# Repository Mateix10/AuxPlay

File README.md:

# AuxPlay
A esp32 based AirPlay receiver for powered speakers. 

Note: This DOES NOT include a amplifier, please connect this device to powered speakers or a speaker amplifier.

# Why?

I always wanted to play music wirelessly to my stereo. It was made in 2001 and it obviously does not have Bluetooth or AirPlay, so I decided to make a device that adds that functionality to it.

# Zine

# Schematic and PCB

For the "brains" I used a older esp32 module because the newer ones don't have classic bluetooth, required for Bluetooth A2DP, aka sound.

For the DAC, I used a PCM-5102 breakout board. Chose it for its sound quality. I used the breakout board for the extra filtering found on there and the ease of soldering it onto the PCB.

The PJ-320B 3.5mm headphone jack is connected through the PCB, using the pins on the DAC breakout board.

# Case

For the case I used Fusion 360. The top part of the case along with the motherboard is screwed in with m2 screws. Preferably, the screws should be long (about 14mm) so it can reach the PCB along with the inserts at the bottom.

# Firmware

For the firmware, I am using [airplay-esp32 by rbouteiller](https://github.com/rbouteiller/airplay-esp32).

# BOM

|Product|Count|Cost|Link|
|--|--|--|--|
|Esp32|1|$17.99|[Freenove Store](https://store.freenove.com/products/fnk0060)
|I2S PCM5102A DAC|1|$2.62|[Aliexpress](https://www.aliexpress.com/item/1005012477247485.html?spm=a2g0o.productlist.main.2.493911331FnOXK&algo_pvid=4adcb7e1-8840-4df3-a0dd-f2ae6f0d7a4f&algo_exp_id=4adcb7e1-8840-4df3-a0dd-f2ae6f0d7a4f-1&pdp_ext_f=%7B%22order%22%3A%2223%22%2C%22eval%22%3A%221%22%2C%22fromPage%22%3A%22search%22%7D&pdp_npi=6%40dis%21USD%212.61%212.61%21%21%2117.68%2117.66%21%40211b61bb17835903966807937e499e%2112000058510522868%21sea%21RO%216479752192%21X%211%210%21n_tag%3A-29919%3Bd%3Ae8b90e1%3Bm03_new_user%3A-29895&curPageLogUid=5Cz8Hdx5unra&utparam-url=scene%3Asearch%7Cquery_from%3A%7Cx_object_id%3A1005012477247485%7C_p_origin_prod%3A)
|PJ-320B DIP Headphone Jack|1|$1.14|[Aliexpress](https://www.aliexpress.com/item/1005002436653862.html?spm=a2g0o.productlist.main.2.7c2f625aUkUTXv&algo_pvid=d1fdaacd-bc8b-40f6-9c8e-081c59262c6e&algo_exp_id=d1fdaacd-bc8b-40f6-9c8e-081c59262c6e-1&pdp_ext_f=%7B%22order%22%3A%2222%22%2C%22spu_best_type%22%3A%22price%22%2C%22eval%22%3A%221%22%2C%22fromPage%22%3A%22search%22%7D&pdp_npi=6%40dis%21USD%211.14%211.14%21%21%211.14%211.14%21%402103867617836015596551588e8313%2112000020655545215%21sea%21RO%216479752192%21X%211%210%21n_tag%3A-29919%3Bd%3Ae8b90e1%3Bm03_new_user%3A-29895&curPageLogUid=Cehayrqnawqp&utparam-url=scene%3Asearch%7Cquery_from%3A%7Cx_object_id%3A1005002436653862%7C_p_origin_prod%3A#nav-specification)
|Screws|1|$7.43|[Aliexpress](https://www.aliexpress.com/item/4000038065691.html?spm=a2g0o.productlist.main.2.4fadfc50T7ugPD&algo_pvid=18ba3291-ada3-4acc-b2ab-eb325b1662f7&algo_exp_id=18ba3291-ada3-4acc-b2ab-eb325b1662f7-1&pdp_ext_f=%7B%22order%22%3A%225087%22%2C%22eval%22%3A%221%22%2C%22fromPage%22%3A%22search%22%7D&pdp_npi=6%40dis%21USD%217.13%217.13%21%21%217.13%217.13%21%40210385db17836340050081368efa4c%2112000031580335588%21sea%21RO%216479752192%21X%211%210%21n_tag%3A-29919%3Bd%3Ae8b90e1%3Bm03_new_user%3A-29895&curPageLogUid=T9XwEPeDqjrQ&utparam-url=scene%3Asearch%7Cquery_from%3A%7Cx_object_id%3A4000038065691%7C_p_origin_prod%3A)
|PCB|1|$2|[JLCPCB](https://jlcpcb.com/)
|Shipping + Tax||$36.65||
|TOTAL||67.83||

# Credits

[Kicad](https://www.kicad.org/) - Schematic and PCB design

[Fusion 360](https://www.autodesk.com/products/fusion-360/overview) - Designing the case

[sstojos's zynthian miniature project](https://github.com/sstojos/zynthian-miniature) - For the footprint and symbol of the PCM5102A DAC module that I used

[airplay-esp32 by rbouteiller](https://github.com/rbouteiller/airplay-esp32) - Firmware

[Hackclub Fallout](https://fallout.hackclub.com) - Founding

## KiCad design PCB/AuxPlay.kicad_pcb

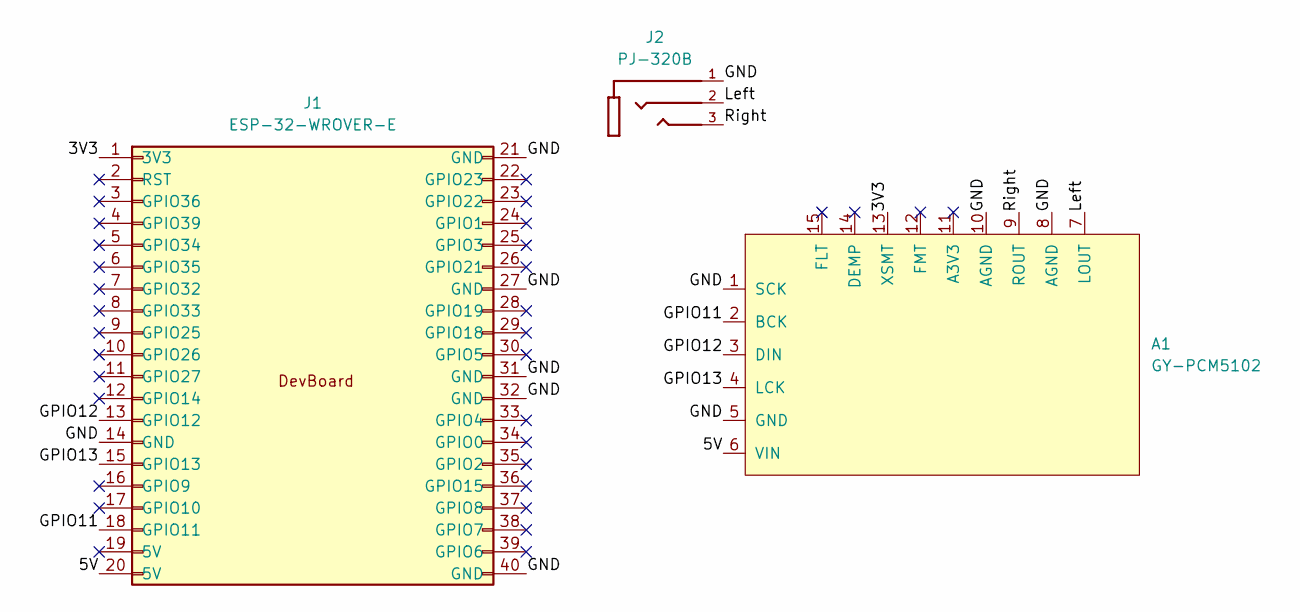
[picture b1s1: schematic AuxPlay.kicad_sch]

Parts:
A1: GY-PCM5102
J1: ESP-32-WROVER-E; Freenove_ESP32-CAM
J2: PJ-320B; BOOMELE_PJ-320B

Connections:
/3V3: A1.13 (XSMT), J1.1 (3V3)
/5V: A1.6 (VIN), J1.20 (5V)
/GND: A1.1 (SCK), A1.5 (GND), A1.8 (AGND), A1.10 (AGND), J1.14 (GND), J1.21 (GND), J1.27 (GND), J1.31 (GND), J1.32 (GND), J1.40 (GND), J2.1
/GPIO11: A1.2 (BCK), J1.18 (GPIO11)
/GPIO12: A1.3 (DIN), J1.13 (GPIO12)
/GPIO13: A1.4 (LCK), J1.15 (GPIO13)
/Left: A1.7 (LOUT), J2.2
/Right: A1.9 (ROUT), J2.3

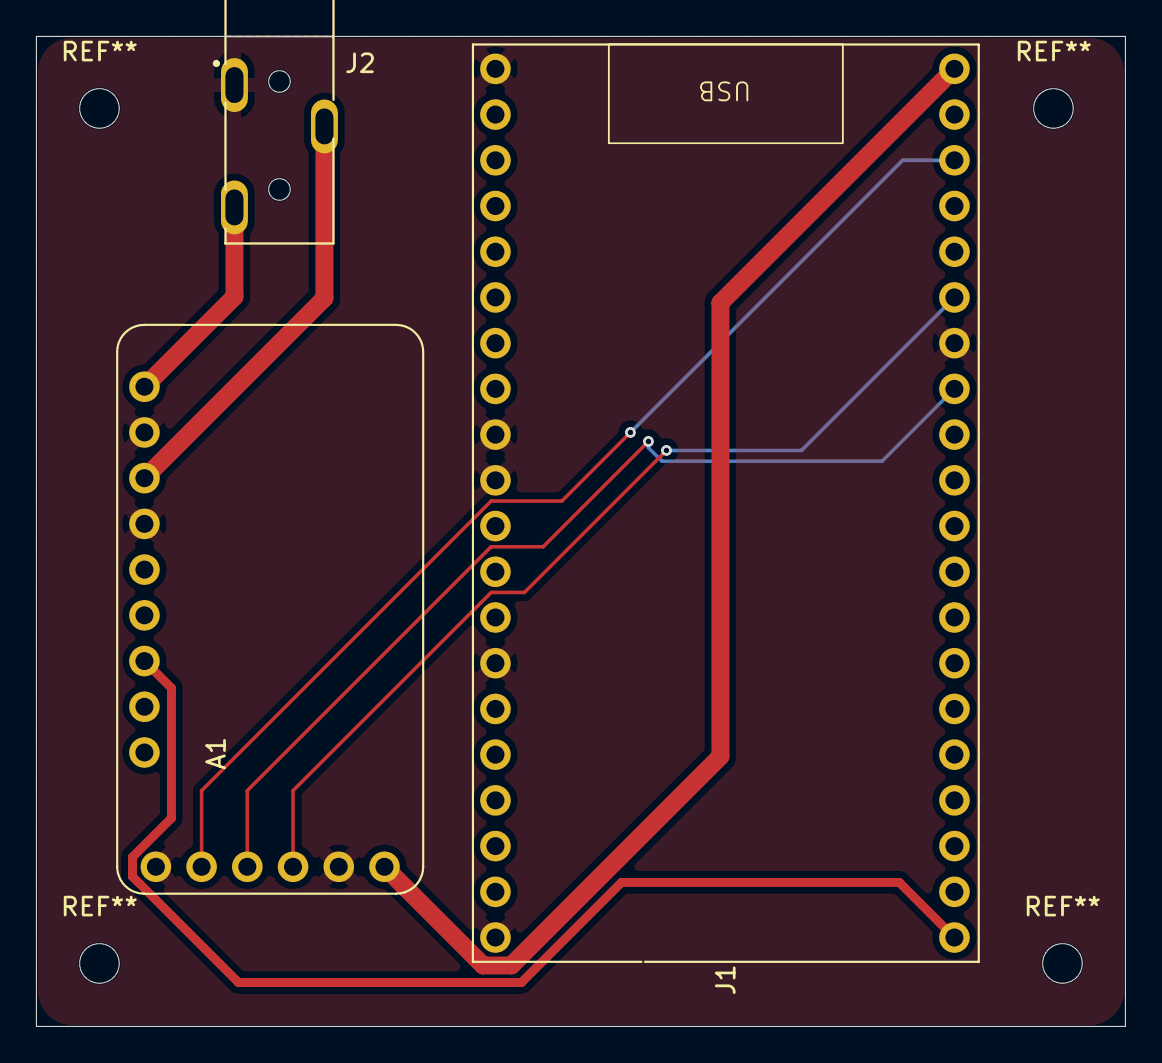
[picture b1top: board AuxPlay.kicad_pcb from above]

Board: 2 copper layers, 60.5 x 55.0 mm, 3 parts (0 on the bottom side), 8 nets.
